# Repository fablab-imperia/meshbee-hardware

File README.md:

# 🐝 MeshBee - Sistema di Monitoraggio Arnie

Hardware

```
meshbee-hardware/
├── 3d-print/     # File CAD per stampa 3D (FreeCAD)
└── pcb/          # Schemi elettrici e documentazione
```

## 📄 Licenza

Questo progetto è distribuito sotto licenza CERN-OHL-S

## 👥 Team

Sviluppato per apicoltori e monitoraggio ambientale.

---

**Fatto con ❤️ per le api** 🐝

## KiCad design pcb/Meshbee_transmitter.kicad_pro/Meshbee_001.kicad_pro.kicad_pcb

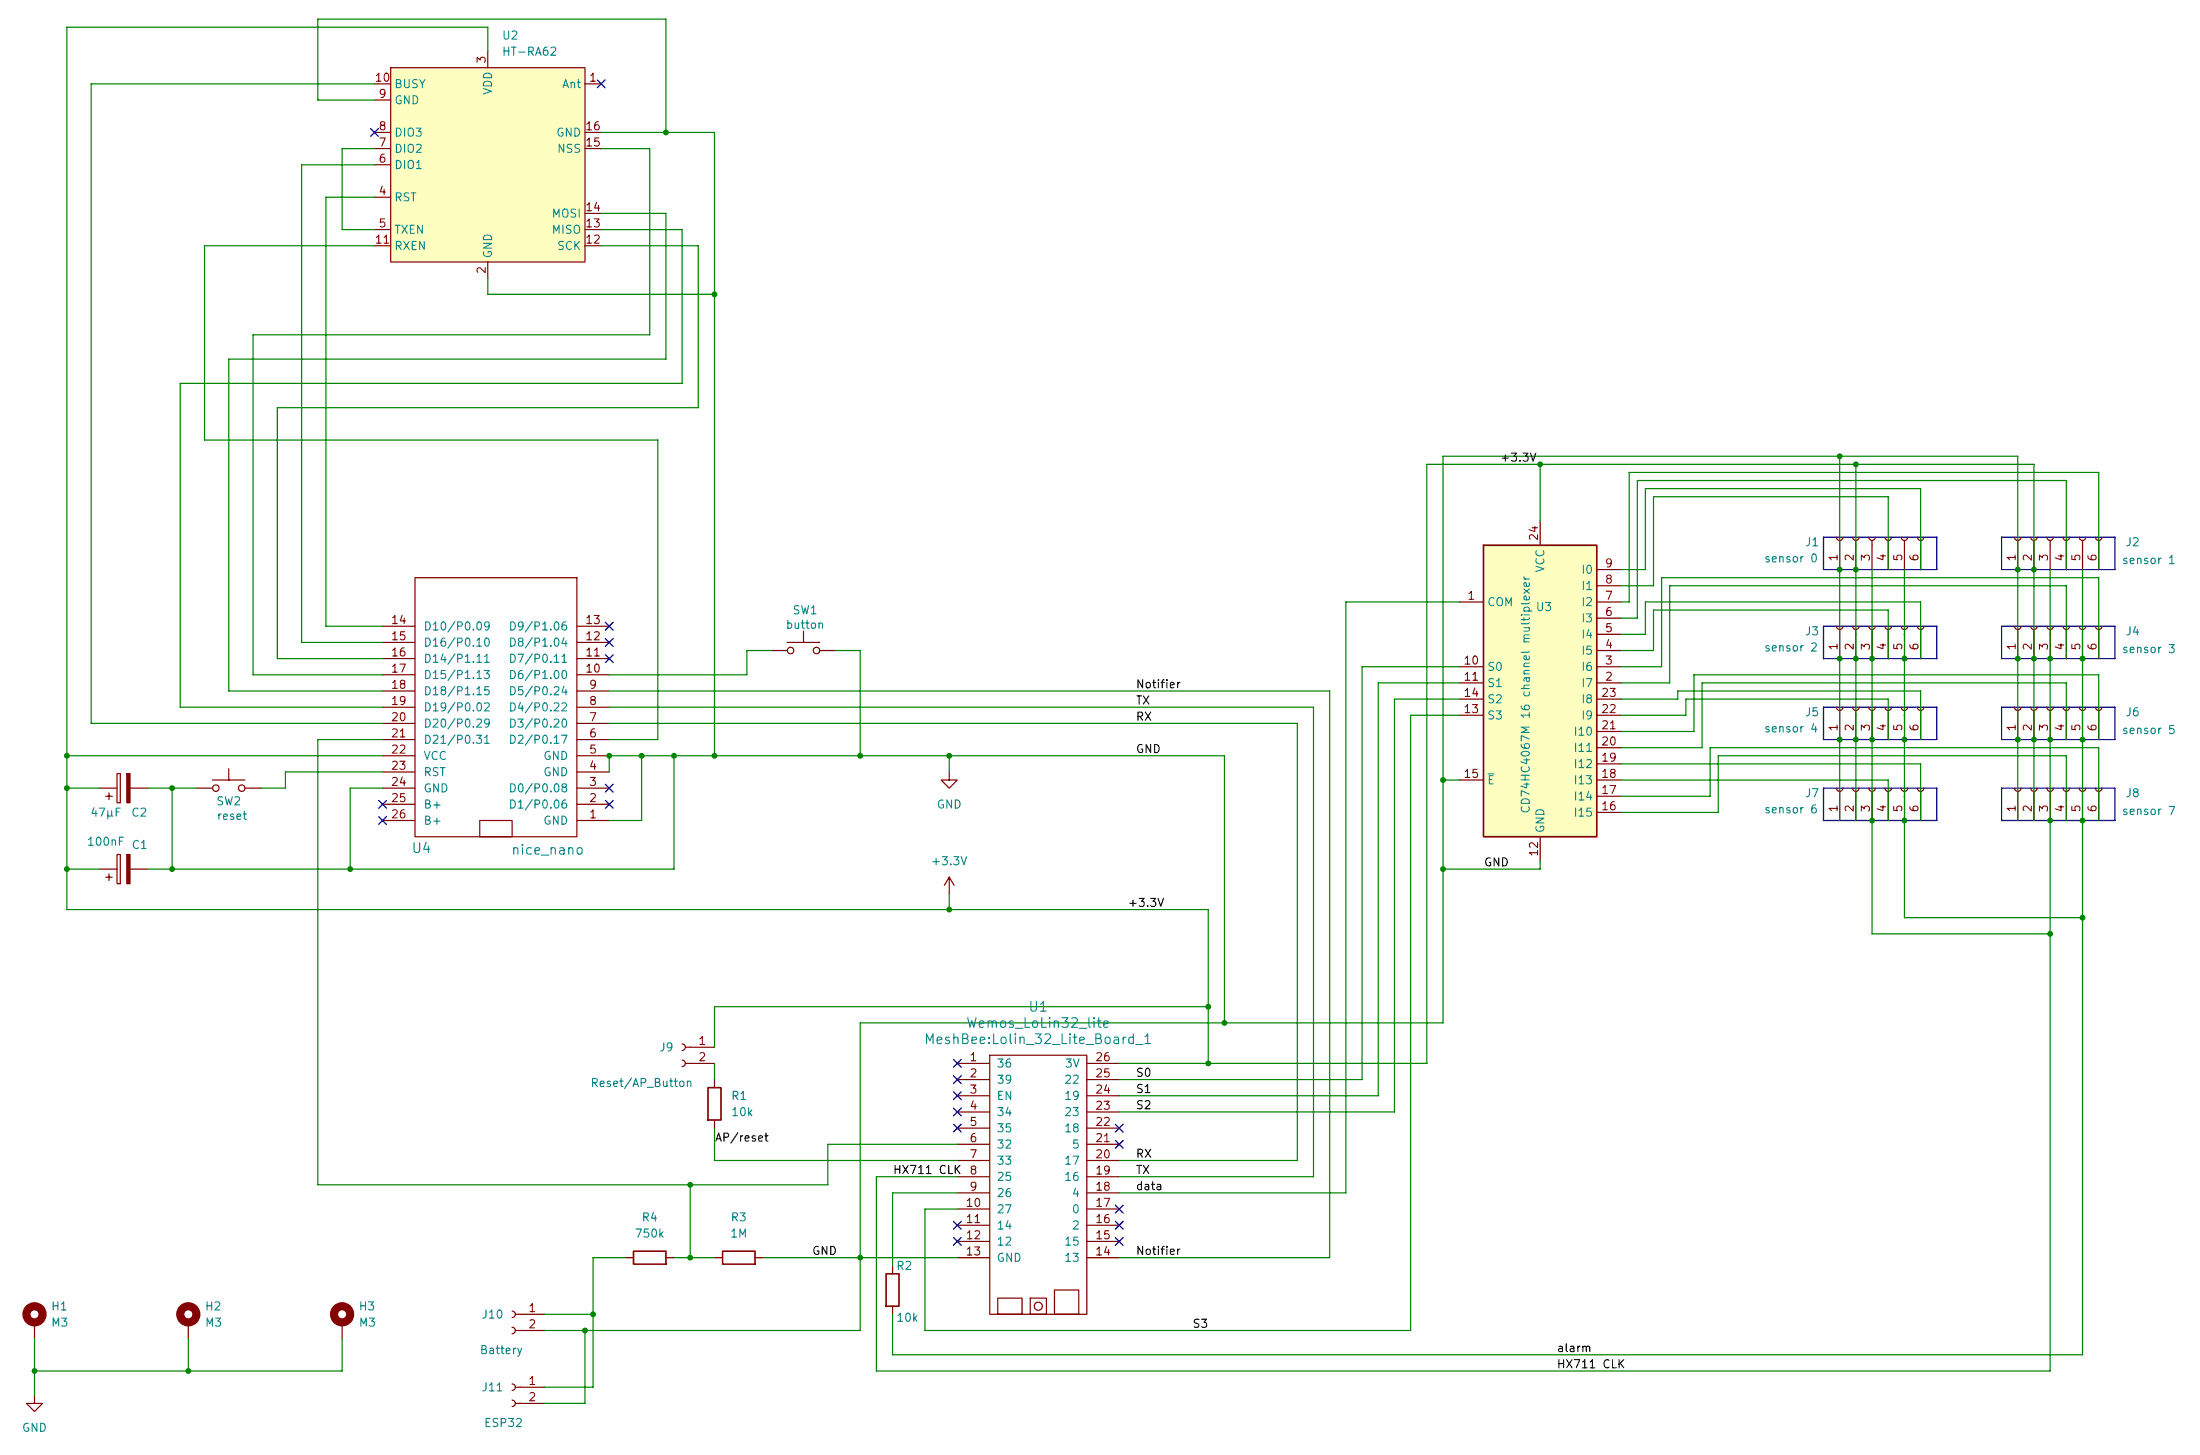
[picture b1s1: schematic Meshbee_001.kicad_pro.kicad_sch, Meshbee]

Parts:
C1: 100nF; CP_Radial_Tantal_D5.0mm_P2.50mm
C2: 47µF; CP_Radial_D5.0mm_P2.00mm
H1, H2, H3: M3; MountingHole_3.2mm_M3_DIN965_Pad
J1: sensor 0; MeshBee_JST_XH_B6B-XH-A_1x06_P2.50mm_Vertical
J2: sensor 1; MeshBee_JST_XH_B6B-XH-A_1x06_P2.50mm_Vertical
J3: sensor 2; MeshBee_JST_XH_B6B-XH-A_1x06_P2.50mm_Vertical
J4: sensor 3; MeshBee_JST_XH_B6B-XH-A_1x06_P2.50mm_Vertical
J5: sensor 4; MeshBee_JST_XH_B6B-XH-A_1x06_P2.50mm_Vertical
J6: sensor 5; MeshBee_JST_XH_B6B-XH-A_1x06_P2.50mm_Vertical
J7: sensor 6; MeshBee_JST_XH_B6B-XH-A_1x06_P2.50mm_Vertical
J8: sensor 7; MeshBee_JST_XH_B6B-XH-A_1x06_P2.50mm_Vertical
J9: Reset/AP_Button; JST_XH_B2B-XH-A_1x02_P2.50mm_Vertical
J10: Battery; JST_XH_B2B-XH-A_1x02_P2.50mm_Vertical
J11: ESP32; JST_XH_B2B-XH-A_1x02_P2.50mm_Vertical
R1, R2: 10k; R_Axial_DIN0204_L3.6mm_D1.6mm_P7.62mm_Horizontal
R3: 1M; R_1206_3216Metric_Pad1.30x1.75mm_HandSolder
R4: 750k; R_1206_3216Metric_Pad1.30x1.75mm_HandSolder
SW1: button
SW2: reset; button
U1: Wemos_LoLin32_lite; Lolin_32_Lite_Board_1
U2: HT-RA62
U3: CD74HC4067M 16 channel multiplexer
U4: nice_nano

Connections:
+3.3V: C1.1, C2.1, J1.2, J2.2, J3.2, J4.2, J5.2, J6.2, J7.2, J8.2, J9.1, U1.26 (3V), U2.3 (VDD), U3.24 (VCC), U4.22 (VCC)
/AP/reset: R1.2, U1.7 (33)
/HX711 CLK: J1.3, J2.3, J3.3, J4.3, J5.3, J6.3, J7.3, J8.3, U1.8 (25)
/Notifier: U1.14 (13), U4.9 (D5/P0.24)
/RX: U1.20 (17), U4.7 (D3/P0.20)
/S0: U1.25 (22), U3.10 (S0)
/S1: U1.24 (19), U3.11 (S1)
/S2: U1.23, U3.14 (S2)
/S3: U1.10 (27), U3.13 (S3)
/TX: U1.19 (16), U4.8 (D4/P0.22)
/alarm: J1.5, J2.5, J3.5, J4.5, J5.5, J6.5, J7.5, J8.5, R2.2
/data: U1.18 (4), U3.1 (COM)
GND: C1.2, C2.2, H1.1 (1_1), H2.1 (1_1), H3.1 (1_1), J1.1, J2.1, J3.1, J4.1, J5.1, J6.1, J7.1, J8.1, J10.2, J11.2, R3.2, SW1.2, SW2.1, U1.13 (GND), U2.2 (GND), U2.9 (GND), U2.16 (GND), U3.12 (GND), U3.15 (~E), U4.1 (GND), U4.4 (GND), U4.5 (GND), U4.24 (GND)
unnamed: J1.4, U3.8 (I1)
unnamed: J1.6, U3.9 (I0)
unnamed: J2.4, U3.6 (I3)
unnamed: J2.6, U3.7 (I2)
unnamed: J3.4, U3.4 (I5)
unnamed: J3.6, U3.5 (I4)
unnamed: J4.4, U3.2 (I7)
unnamed: J4.6, U3.3 (I6)
unnamed: J5.4, U3.22 (I9)
unnamed: J5.6, U3.23 (I8)
unnamed: J6.4, U3.20 (I11)
unnamed: J6.6, U3.21 (I10)
unnamed: J7.4, U3.18 (I13)
unnamed: J7.6, U3.19 (I12)
unnamed: J8.4, U3.16 (I15)
unnamed: J8.6, U3.17 (I14)
unnamed: J9.2, R1.1
unnamed: J10.1, J11.1, R4.1
unnamed: R2.1, U1.9 (26)
unnamed: R3.1, R4.2, U1.6 (32), U4.21 (D21/P0.31)
unnamed: U2.10 (BUSY), U4.20 (D20/P0.29)
unnamed: U2.6 (DIO1), U4.15 (D16/P0.10)
unnamed: U2.5 (TXEN), U2.7 (DIO2)
unnamed: U2.13 (MISO), U4.19 (D19/P0.02)
unnamed: U2.14 (MOSI), U4.18 (D18/P1.15)
unnamed: U2.15 (NSS), U4.17 (D15/P1.13)
unnamed: U2.4 (RST), U4.14 (D10/P0.09)
unnamed: U2.11 (RXEN), U4.6 (D2/P0.17)
unnamed: U2.12 (SCK), U4.16 (D14/P1.11)
unnamed: SW1.1, U4.10 (D6/P1.00)
unnamed: SW2.2, U4.23 (RST)

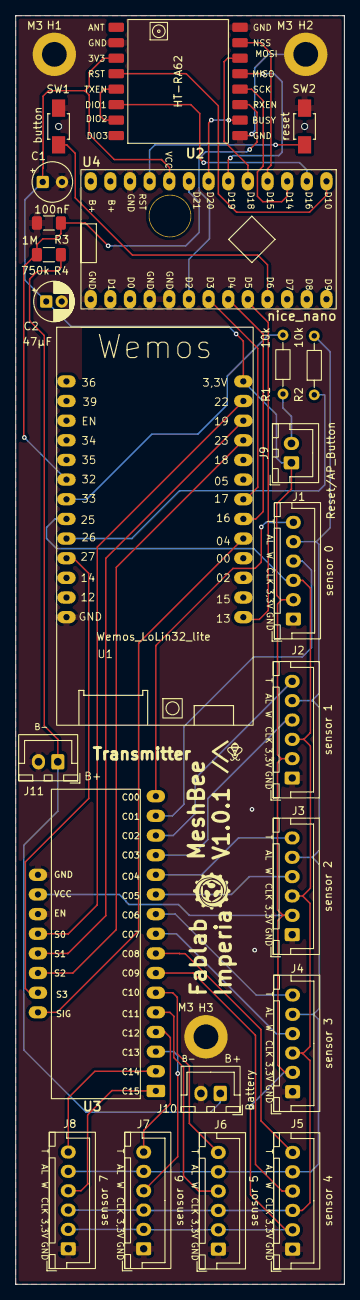
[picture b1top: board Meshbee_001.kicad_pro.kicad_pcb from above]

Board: 2 copper layers, 42.5 x 164.0 mm, 26 parts (0 on the bottom side), 44 nets.
